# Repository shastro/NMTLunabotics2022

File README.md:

# NMTLunabotics2022
Primary Repository for All Software related to NMT Lunabotics 2022.

Please check the docs folder for relevant documentation and store user code in the user folder.

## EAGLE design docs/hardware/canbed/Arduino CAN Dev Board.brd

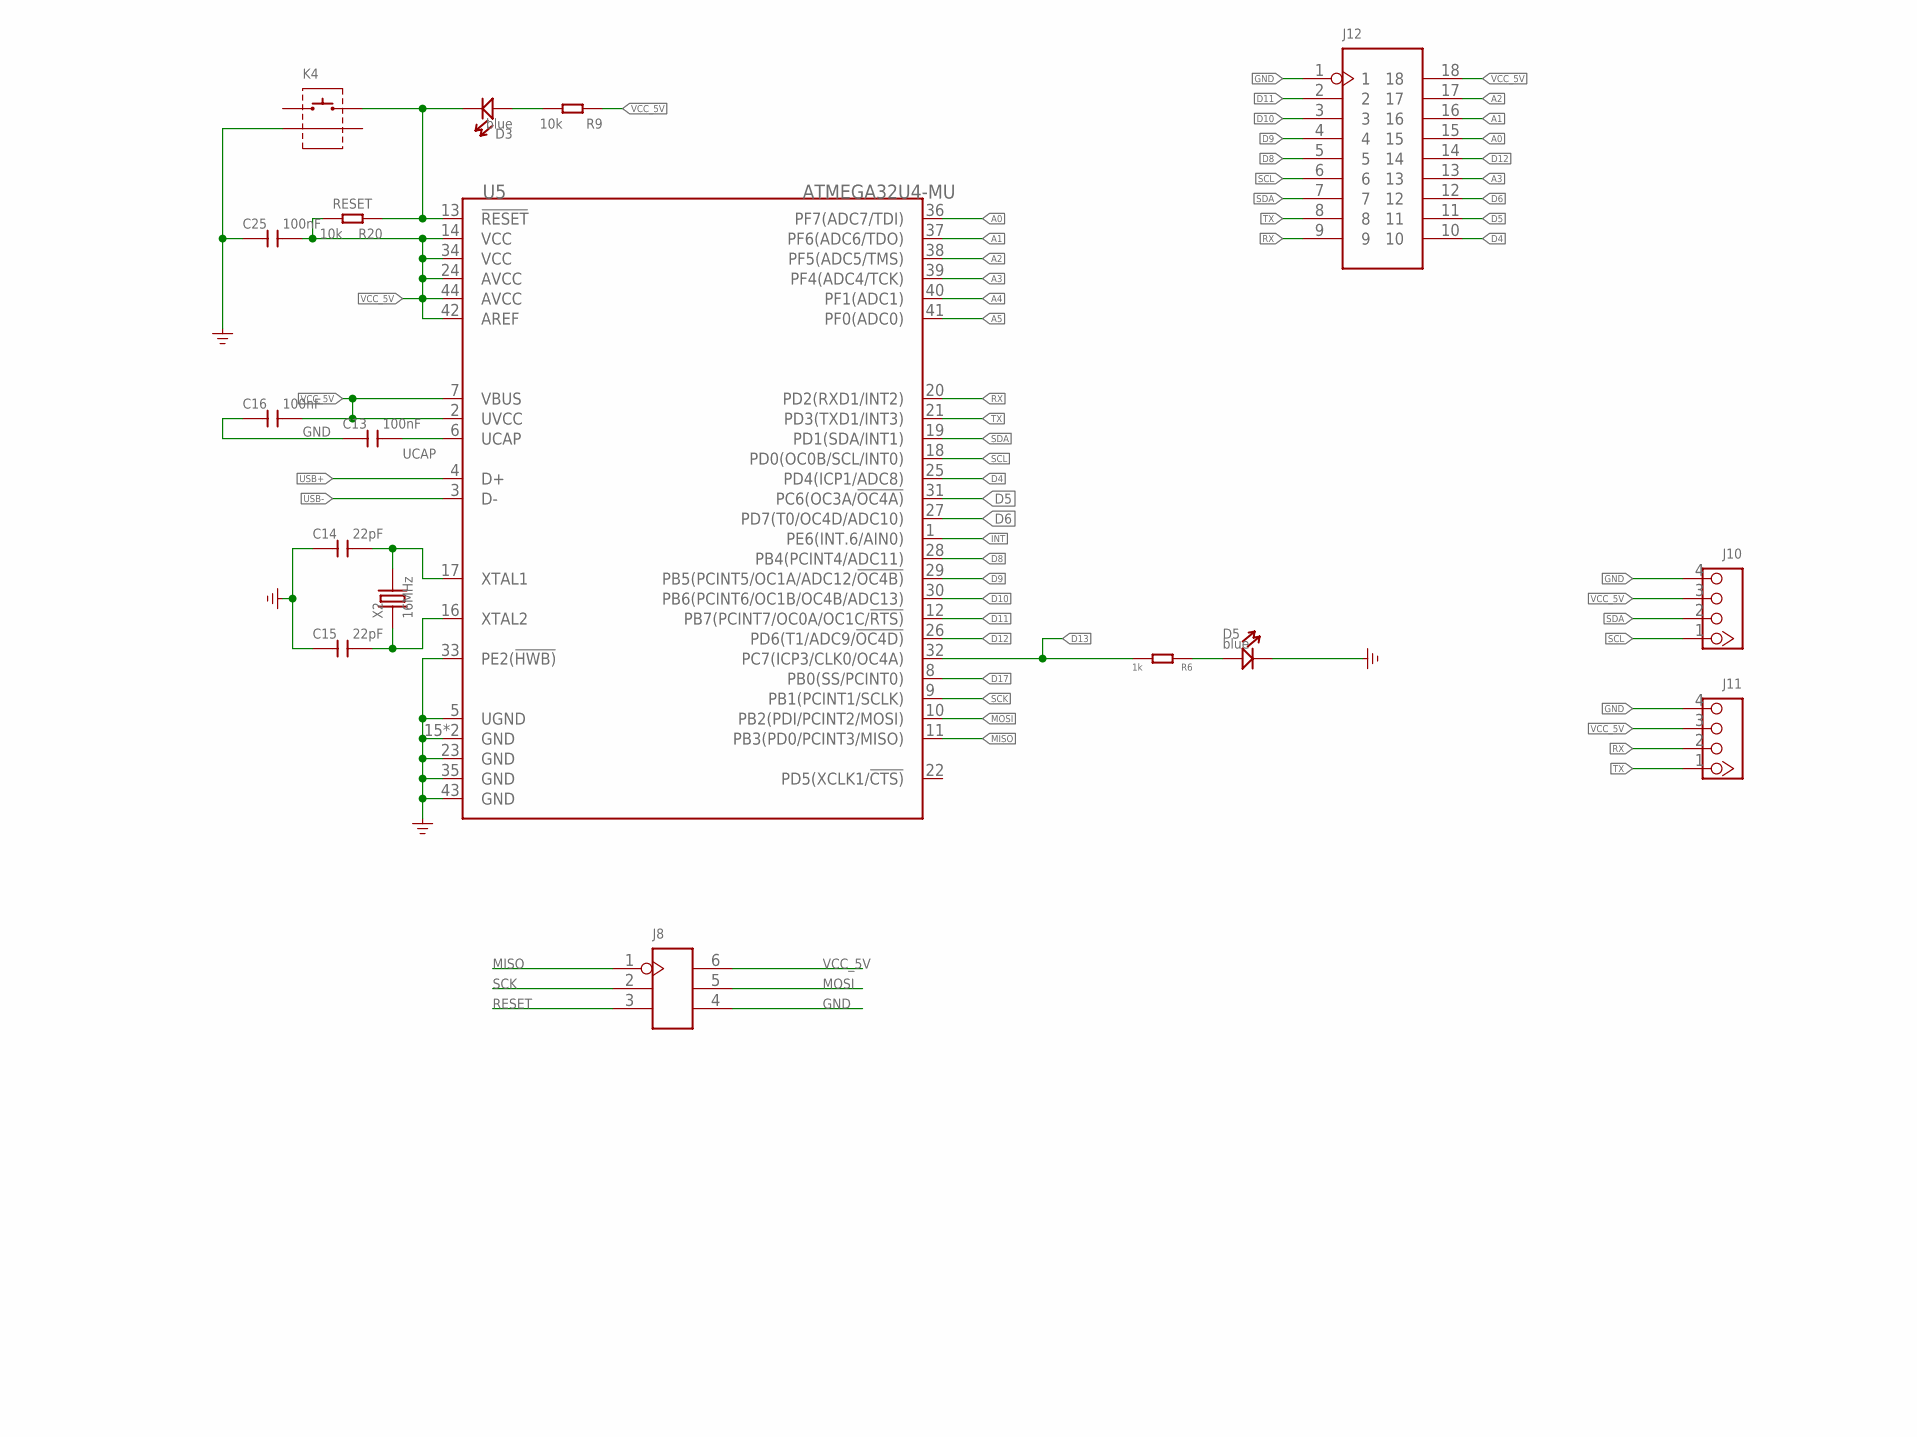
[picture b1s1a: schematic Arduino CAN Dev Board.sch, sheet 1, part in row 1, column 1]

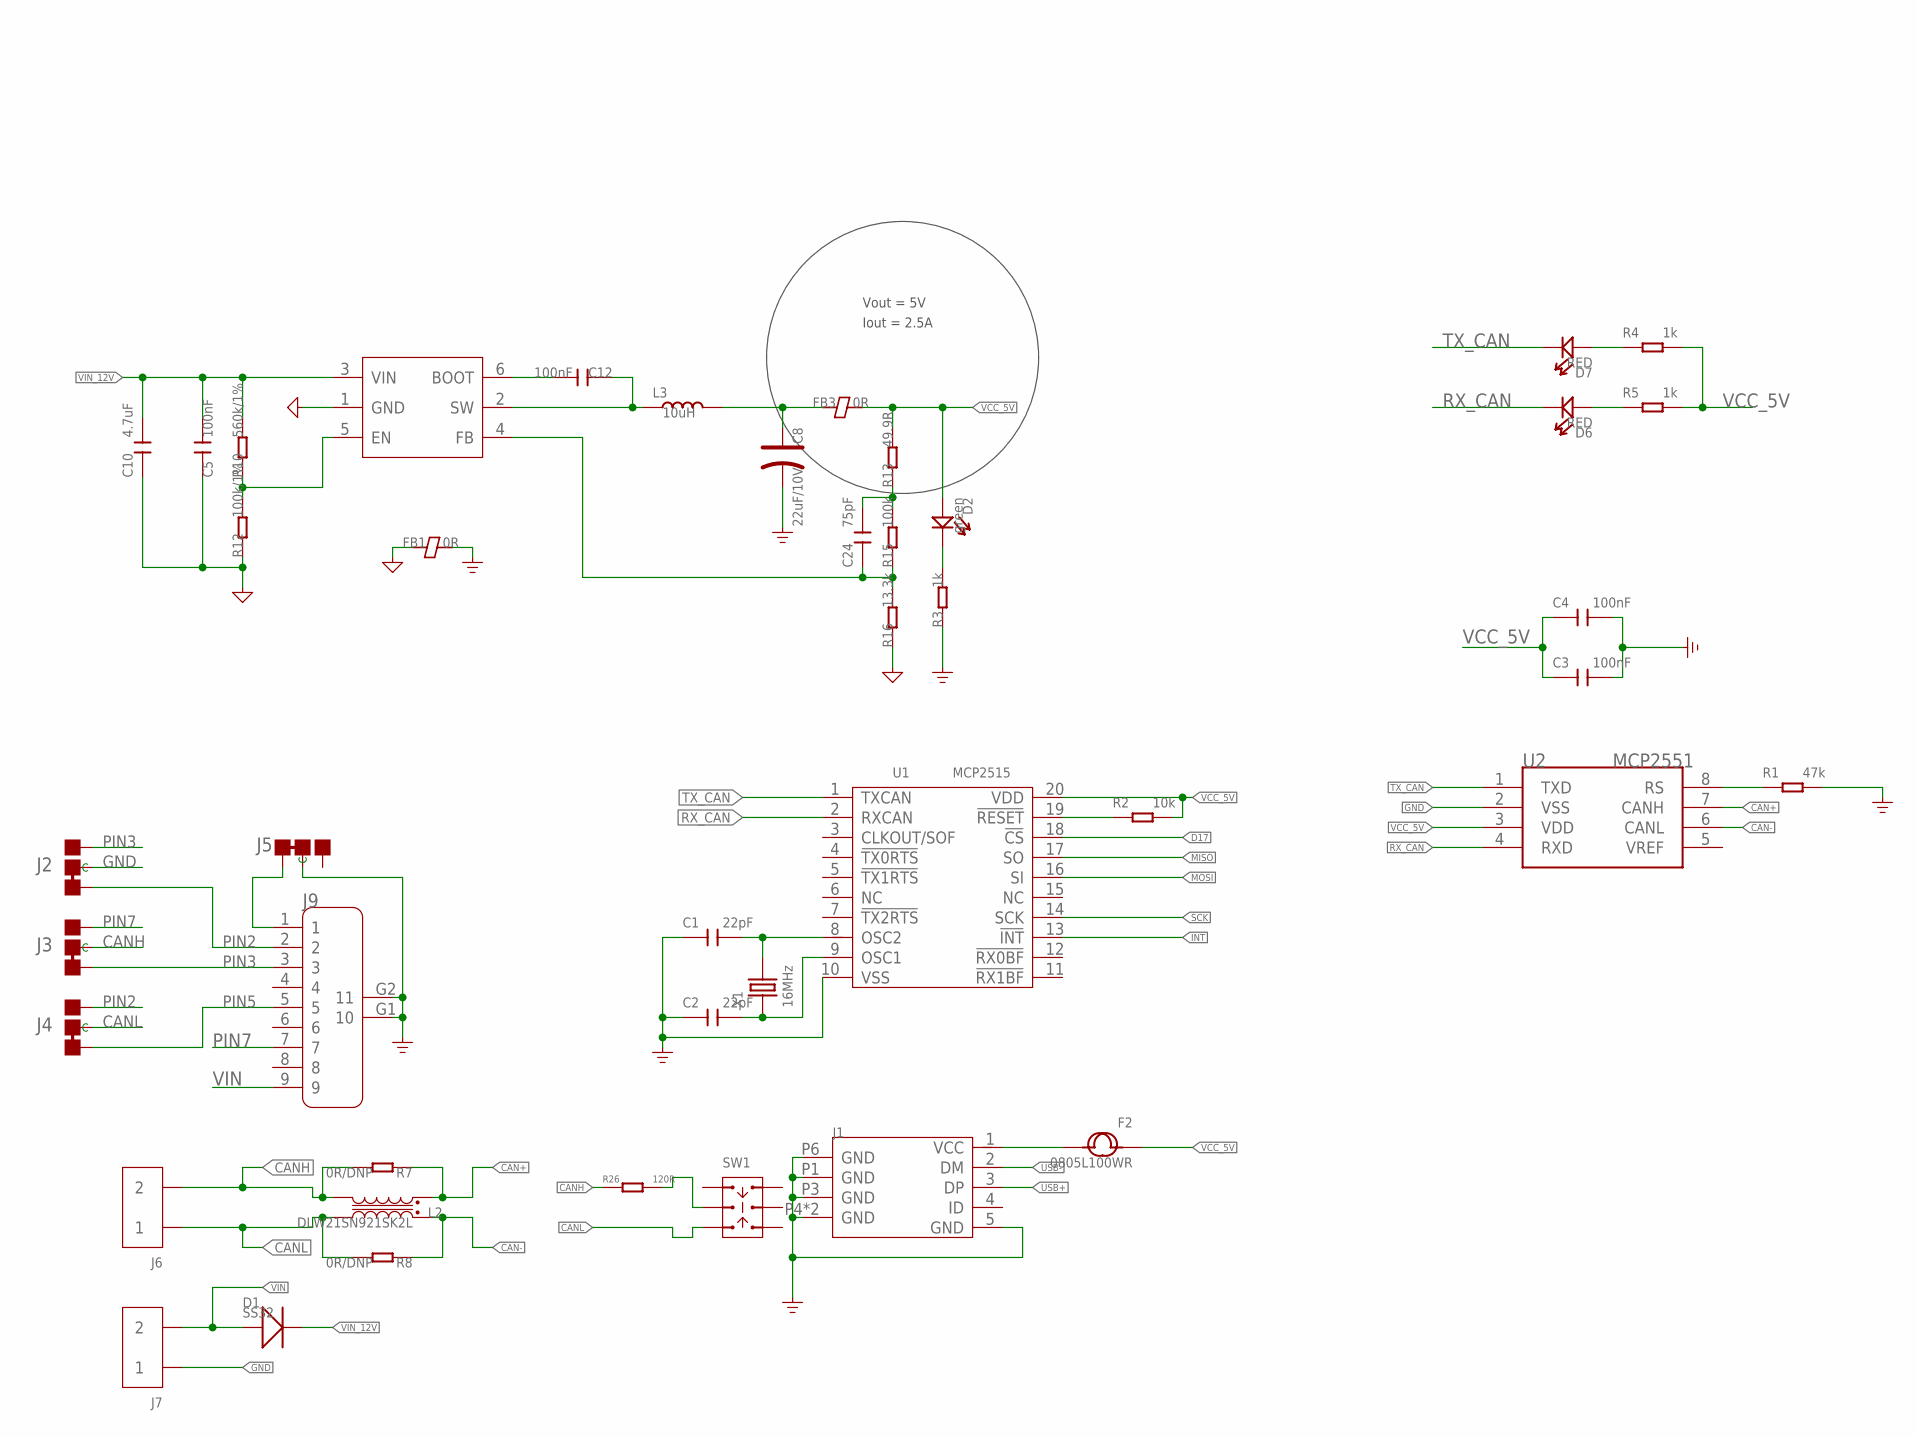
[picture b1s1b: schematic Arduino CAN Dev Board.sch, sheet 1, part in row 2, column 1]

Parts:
C1, C2, C14, C15: 22pF; C0603
C3, C4, C5, C12, C13, C16, C25: 100nF; C0603
C8: 22uF/10V; AVX-B
C10: 4.7uF; C1206
C24: 75pF; C0603
D1: SS32; DO-214AC
D2: green; LED-0603
D3, D5: blue; LED-0603
D6, D7: RED; LED-0603
F2: 0805L100WR; F0805
FB1, FB3: 0R; F0805
J1: MICRO-USB5+4P-320010050; MICRO-USB5+5P-SMD-0.65-7.2X5.06MM
J2, J3, J4, J5: JUMPER-3P-SHORT; 3P-SMD-SHORT
J6, J7: SCREW-TERMINAL-2P'5.08'; H2-5.0-10.5X8.0MM
J8: HEADER-2X3P-2.54; H2X3-2.54
J9: DB9'MEAL'; DB9-MEAL
J10, J11: 320110033; HW4-2.0
J12: HEADER-2X9P-2.54; H2X9-2.54
K4: BUTTON-2+2P; SW2+2P-7.7X2.75X3.95MM
L2: DLW21SN921SK2L; INT4-0.85-2X1.25X1.2MM
L3: 10uH; INT2-SMD-6.6X7.1X3MM
R1: 47k; R0603
R2, R9, R20: 10k; R0603
R3, R4, R5, R6: 1k; R0603
R7, R8: 0R/DNP; R0603
R10: 560k/1%; R0603
R12: 100k/1%; R0603
R13: 49.9R; R0603
R15: 100k; R0603
R16: 13.3k; R0603
R26: 120R; R0603
SW1: SWITCH-2CH-6P-311010004; SW6-2.54-9.0X3.5X3.2+2.0MM
U1: MCP2515; TSSOP20-0.65-6.5X4.4MM
U2: MCP2551; SOIC8-6.0
U5: ATMEGA32U4-MU; QFN44
U$11: PMIC-TPS54302; SOT-23-6
X1: 16MHz; X2-SMD-5.0X3.2X1.3MM
X2: 16MHz; 2P-SMD-5X3.2

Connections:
A0: J12.15, U5.36 (PF7(ADC7/TDI))
A1: J12.16, U5.37 (PF6(ADC6/TDO))
A2: J12.17, U5.38 (PF5(ADC5/TMS))
A3: J12.13, U5.39 (PF4(ADC4/TCK))
A4: U5.40 (PF1(ADC1))
A5: U5.41 (PF0(ADC0))
AGND: C5.1, C10.1, FB1.1, R12.1, R16.1, U$11.1 (GND)
CAN+: L2.4, R7.1, U2.7 (CANH)
CAN-: L2.1, R8.1, U2.6 (CANL)
CANH: J3.MM (C), J6.2, L2.3, R7.2, R26.1
CANL: J4.MM (C), J6.1, L2.2, R8.2, SW1.CH1B
D4: J12.10, U5.25 (PD4(ICP1/ADC8))
D5: J12.11, U5.31 (PC6(OC3A/!OC4A))
D6: J12.12, U5.27 (PD7(T0/OC4D/ADC10))
D8: J12.5, U5.28 (PB4(PCINT4/ADC11))
D9: J12.4, U5.29 (PB5(PCINT5/OC1A/ADC12/!OC4B))
D10: J12.3, U5.30 (PB6(PCINT6/OC1B/OC4B/ADC13))
D11: J12.2, U5.12 (PB7(PCINT7/OC0A/OC1C/!RTS))
D12: J12.14, U5.26 (PD6(T1/ADC9/!OC4D))
D13: R6.2, U5.32 (PC7(ICP3/CLK0/OC4A))
D17: U1.18 (!CS), U5.8 (PB0(SS/PCINT0))
EXT_PWR: F2.2, J1.1 (VCC)
GND: C1.1, C2.1, C3.2, C4.2, C8.-, C13.1, C14.1, C15.1, C16.1, C25.1, D5.-, FB1.2, J1.5 (GND), J1.P1 (GND), J1.P3 (GND), J1.P4 (GND), J1.P5 (GND), J1.P6 (GND), J2.MM (C), J5.MM (C), J7.1, J8.4, J9.G1 (10), J9.G2 (11), J10.4, J11.4, J12.1, K4.S1, R1.2, R3.1, U1.10 (VSS), U2.2 (VSS), U5.5 (UGND), U5.15 (GND), U5.23 (GND), U5.33 (PE2(!HWB)), U5.35 (GND), U5.43 (GND), U5.TAB (GND)
INT: U1.13 (!INT), U5.1 (PE6(INT.6/AIN0))
MISO: J8.1, U1.17 (SO), U5.11 (PB3(PD0/PCINT3/MISO))
MOSI: J8.5, U1.16 (SI), U5.10 (PB2(PDI/PCINT2/MOSI))
unnamed: D2.-, R3.2
unnamed: D7.+, R4.1
unnamed: D3.+, R9.2
unnamed: R10.1, R12.2, U$11.5 (EN)
unnamed: R26.2, SW1.COM1
unnamed: C14.2, U5.17 (XTAL1), X2.2
unnamed: D5.+, R6.1
unnamed: C12.1, L3.1, U$11.2 (SW)
unnamed: C15.2, U5.16 (XTAL2), X2.1
unnamed: J5.11 (L), J9.1
unnamed: C12.2, U$11.6 (BOOT)
unnamed: D6.+, R5.1
unnamed: C1.2, U1.8 (OSC2), X1.2
unnamed: C2.2, U1.9 (OSC1), X1.1
unnamed: C8.+, FB3.1, L3.2
unnamed: R1.1, U2.8 (RS)
unnamed: C24.2, R13.1, R15.2
unnamed: C24.1, R15.1, R16.2, U$11.4 (FB)
PIN2: J2.11 (L), J4.00 (R), J9.2
PIN3: J2.00 (R), J3.11 (L), J9.3
PIN5: J4.11 (L), J9.5
PIN7: J3.00 (R), J9.7
RESET: D3.-, J8.3, K4.2, R20.1, U5.13 (!RESET)
RST_N: R2.1, U1.19 (!RESET)
RX: J11.2, J12.9, U5.20 (PD2(RXD1/INT2))
RX_CAN: D6.-, U1.2 (RXCAN), U2.4 (RXD)
SCK: J8.2, U1.14 (SCK), U5.9 (PB1(PCINT1/SCLK))
SCL: J10.1, J12.6, U5.18 (PD0(OC0B/SCL/INT0))
SDA: J10.2, J12.7, U5.19 (PD1(SDA/INT1))
TX: J11.1, J12.8, U5.21 (PD3(TXD1/INT3))
TX_CAN: D7.-, U1.1 (TXCAN), U2.1 (TXD)
UCAP: C13.2, U5.6 (UCAP)
USB+: J1.3 (DP), U5.4 (D+)
USB-: J1.2 (DM), U5.3 (D-)
VCC_5V: C3.1, C4.1, C16.2, C25.2, D2.+, F2.1, FB3.2, J8.6, J10.3, J11.3, J12.18, R2.2, R4.2, R5.2, R9.1, R13.2, R20.2, U1.20 (VDD), U2.3 (VDD), U5.2 (UVCC), U5.7 (VBUS), U5.14 (VCC), U5.24 (AVCC), U5.34 (VCC), U5.42 (AREF), U5.44 (AVCC)
VIN: D1.1 (+), J7.2, J9.9
VIN_12V: C5.2, C10.2, D1.2 (-), R10.2, U$11.3 (VIN)

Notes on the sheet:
Vout = 5V
Iout = 2.5A

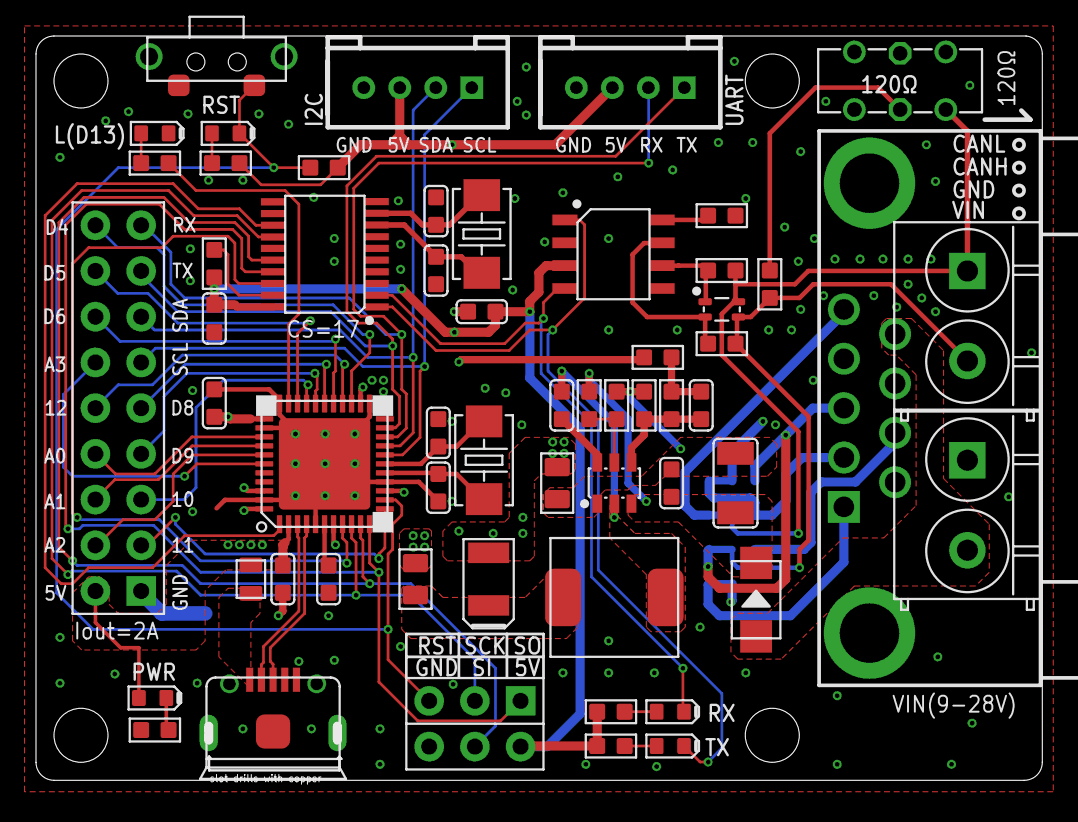
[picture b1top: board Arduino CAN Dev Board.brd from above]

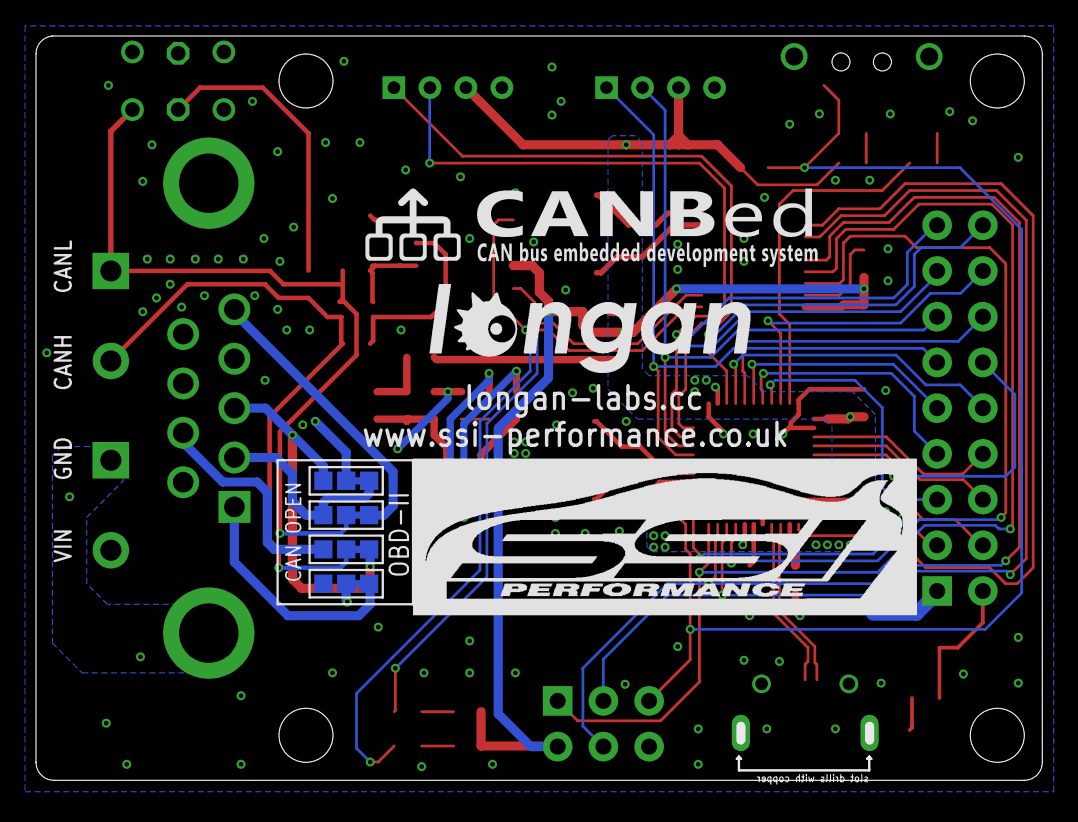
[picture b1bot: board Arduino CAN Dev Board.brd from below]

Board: 2 copper layers, 55.4 x 41.2 mm, 62 parts (5 on the bottom side), 61 nets.

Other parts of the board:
U$12: LONGAN-SILK-SMALL

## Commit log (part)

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2021-10-28 Add c generation tests as well as a script for generating linear maps for use in the kcd files. Add first successful custom kcd file x.kcd
2021-10-29 Add preliminary can2canarray code (Currently just recieves can msgs via socketcan. Add testing kcd file x.kcd. Add CAN interface setupscript
2021-10-31 Speed controls in robot_kbd
2021-10-31 Make robot resemble Lunabotics slightly better
    I'm using four wheels on each side to try and vaguely approximate
    how treads will operate.
2021-11-09 Fix controller node name
2021-11-09 Restructure CAN demos
2021-11-10 Use vector of wheels
2021-11-13 Probably fix compilation issues on Ubuntu
    There's an issue with the generic syntax I'm using on the Ubuntu C++
    compiler. This should /probably/ fix it, but I'm not 100% sure.
2021-11-17 Put some sensors on the robot
2021-11-18 Add .weproj file
2021-11-23 :memo: Shameless change to test gitmoji don't @me
2021-11-25 Update Ubuntu20_Demo_Instructions.md
    Add ROS install instructions
2021-11-25 Update Ubuntu20_Demo_Instructions.md
    Add Webots, ROS, and Demo sections
2021-11-25 Update Ubuntu20_Demo_Instructions.md
    Update Readme
2022-01-04 Move to catkin workspace, create user directory with tutorial files
2022-01-21 Update Ubuntu20_Demo_Instructions.md
    Updated the directory pointing to robot_kbd
2022-01-28 Add rplidar_ros
2022-01-28 Fix robot_kbd quitting behavior
    No idea why it was like that originally, but it was bugging me.
2022-01-30 Update Readme.md
    Testing webhook
2022-01-30 Start base controller dev
2022-01-30 Write base controller
2022-01-30 Fix copyright
2022-01-31 Add `cmd-vel-path` argument to base controller
2022-01-31 Add nav_dummy program for testing base controller
2022-02-02 Update lidardemo to Webots 2022a
    Update wheel rotations to FLU/ENU axis system; this will be
    incompatible with 2021b (the previous version), so everyone will have
    to update.
2022-02-04 Add launch file. Add aruco tests.
2022-02-04 abethel: add formatting script
2022-02-04 Factor out transforms into their own launch file
2022-02-04 Add webcam support for arucoTest
2022-02-06 :bulb: Add launch comment
2022-02-08 Add aruco tests, Add sim tests
2022-02-09 Nav stack config work (still not quite done)
2022-02-10 Fix tf issue. Add maps.
2022-02-10 Update use tf2 instead of tf
2022-02-10 :beers: Move files, Correct parameters for robot nav stack configs.
2022-02-10 Fix transforms
2022-02-10 Move launch, maps, configs,rviz, etc to ros package
2022-02-10 Remove extra files
2022-02-11 Fix sim launch file
2022-02-11 Update params, moving towards navstack in webots
2022-02-12 Formatting
2022-02-18 Move TLDR to docs
2022-02-18 Update tldr
2022-02-25 Fix sim models
2022-02-25 Update world
2022-02-28 Remove inner set of 4 wheels on simulation robot
    This commit removes wheels 5, 6, 7, and 8 on all the simulation
    robots, and removes all code that controls those wheels from
    base_controller and robot_kbd. This should provide a starting point
    for fixing the issues with slipping when the robot is navigating.
2022-03-14 Add tracks to TEST_FLAT Webots file
    Have yet to get them actually spinning correctly.
2022-03-18 Updates to robots. Have made a new robot in tracked_animated.wbt but it still does not move
2022-03-18 Replaced old robot with new robot
2022-03-18 Added robots folder to make it easier to modify and import david into different worlds
2022-03-21 Automatically load the RVIZ configuration
2022-03-21 Straighten camera orientation in TEST_FLAT
    It was really bugging me :P
2022-03-22 Set up `sim_basic.sh` with the laser
    Mapping seems to work again :)
2022-03-22 Update rviz config for sim
2022-03-22 Get `move_base` working on current robot
    For some reason it spins around forever rather than actually
    navigating, but it is apparently running.
2022-03-23 Movebase working. Update footprint. Update rviz
2022-03-23 Update rviz update global costmap
2022-03-23 Set motor radius to theoretically correct value
    Hmm
2022-03-31 Update costmap params
2022-03-31 Add new hardware docs
2022-03-31 Add aruco experiments
2022-04-05 Add system parts blend files
2022-04-05 Removed extra files
2022-04-07 Fix rplidar_ros not existing
2022-04-09 Add bluetooth controller experiments, motor experiments, and action server experiments
2022-04-09 Replace `backup` with `rpi-clone`
2022-04-09 Clean up base_controller code
2022-04-10 Implement basic motor control over bluetooth. Needs refactoring and code organization
2022-04-15 Rename folder
2022-04-15 Fix folder name
2022-04-15 Fixed? xr_usb_serial_common driver error
2022-04-15 Fix typo in driver
2022-04-15 Start Teknic integration in base_controller
2022-04-15 Wheee broken dependencies
2022-04-15 Remove more Webots dependencies
2022-04-16 More work on Teknic base_controller integration
2022-04-16 Refactor motor_bluetooth stuff
2022-04-17 Add setNodePos function to motor_bluetooth
2022-04-17 Write Raspberry Pi GPIO library
2022-04-18 GPIO input & output pin abstraction
2022-04-19 Don't tear the robot apart, Alex
2022-04-19 Fix rpm
2022-04-20 Update motor values
2022-04-20 Fix incorrect comments
2022-04-20 Override motor velocity to -5
2022-04-20 Debugging shenanigans
2022-04-26 Fix `joystick.cc` move constructor unsoundness
    If I ever get around to it I'll file a bug report with the original
    library that the move constructor is unsound.
2022-04-27 Remove moveNodesFixed -> setAllNodeVel
2022-04-27 Remove comments
2022-04-27 Ensure ports disable motors before disconnecting
    Previous code likely caused a soundness bug.
2022-04-27 Motor lib documentation
2022-04-29 Reorganize motor_bluetooth
2022-04-30 Add camera test
2022-04-30 Remove object files accidentally included
2022-04-30 Use move semantics on nodes & ports
2022-05-10 Add abethel test_workspace
2022-05-11 Add fibonacci client
2022-05-11 Write compile commands
2022-05-11 david_action Navigation action stuff
2022-05-11 Update webots worlds
2022-05-11 Add david_waypoints skeleton
2022-05-11 Fix incorrect david_waypoints CMakeLists
2022-05-11 Update parameters and movebase
2022-05-11 Write skeleton pitch action
2022-05-12 Update motor_bluetooth for temporary setup
2022-05-12 Set up for test without dump motors
2022-05-12 Teknic ROS integration
2022-05-12 Update navigation
2022-05-12 Fix error handling in motor_bluetooth
2022-05-12 Fix EnableReq
2022-05-12 Increase locomotion velocity
2022-05-12 Fix same bug in base_controller
2022-05-12 Add motor property reads
2022-05-12 Add rms level
2022-05-13 More error handling 😤
2022-05-13 Code formatting
2022-05-13 Use symlinks for motor_lib
2022-05-13 Add cvcam.py
2022-05-13 Navigation server implementation skeleton
2022-05-13 Remove old aruco test
2022-05-13 Add urdfs
2022-05-13 Use image_transport
2022-05-13 Add dump tranforms
2022-05-14 Create pitch_controller package
2022-05-14 Write pitch test under user/abethel
2022-05-14 Emergency commit
2022-05-14 Better pitch test UI
2022-05-14 Fix raspberry pi GPIO race condition >:(
2022-05-14 Add pitch assembly
2022-05-14 Improve joint naming convention
2022-05-14 Update pitch controller
2022-05-14 Update urdfs
2022-05-14 david_action pitch GPIO support
2022-05-14 Typo
2022-05-14 Wait 50 seconds for pitch changes
2022-05-14 Add comments
2022-05-14 Add test_urdf.launch
2022-05-15 Added script to point ROS_MASTER_URI at demo pi
2022-05-15 Action tests program
2022-05-15 Fix waiting for action server
2022-05-15 Fix angle in pitch server
2022-05-15 Finish params
2022-05-15 Update launch file and urdf
2022-05-15 Fix joint state launch file
2022-05-15 Add progress
2022-05-15 Finalize progress on pitch action server
2022-05-15 Teknic motor manager to prevent RMS overload
2022-05-15 Fix float cast
2022-05-15 Fix clock bug
2022-05-15 Add print statement
2022-05-15 Fix clock thingy
2022-05-15 Add debug print
2022-05-15 Update time_wait signature
2022-05-15 Move base_controller to david_motor directory
2022-05-15 Replace base_controller in temp_sim.launch
2022-05-15 Fix sign error
2022-05-15 Add new david_motor message defs
2022-05-15 Fix input handling
2022-05-15 Fix compilation error
2022-05-15 Add david_hello network test package
2022-05-15 Change image encoding
2022-05-16 Add udp options to prevent overrun errors
2022-05-16 Adding hardware timer interrupts for status LED. LED now blinks when device in standby; solid when enable pin held high.
2022-05-16 Added shell script for updating Arduino code. Script copiles latest version of .ino code and programs the Arduino.
2022-05-16 Add camera utility program skeleton. Update Waypoints.
2022-05-16 Fix merge aaaaaaaa
2022-05-16 Added verbose flag to Arduino programming script.
2022-05-16 Fix CMakeLists
2022-05-16 Added interrupt-driven enable pin polling. The state of the enable pin is now polled at 2kHz using timer interrupt. Enable pin state is also debounced.
2022-05-16 Fix udp string
2022-05-16 Fixed erroneous mode input evaluation.
2022-05-16 Separate out cmd_auger and cmd_dump
2022-05-16 Add camera calibration and update testing utils
2022-05-16 Remove fifo_size as it seems to be another source of delay
2022-05-16 Further camera property adjustments
2022-05-16 Get david_gamepad working
2022-05-17 Adjust udp options
2022-05-17 💩 Implement david_motor APIs
2022-05-17 Use <> instead of "" in david_motor
    may or may not resolve build issues
2022-05-17 Fix david_gamepad depth commands
2022-05-17 Update projection axis
2022-05-17 Functionalized actuator control scheme.
2022-05-17 In Arduino code, made HalfExtend() state-aware. Also accounted for transition from full-extend to half-extend states.
2022-05-17 Error correction in motors
2022-05-17 Update arduino code for fancy shmancy H-bridges
2022-05-17 Revert reversion because cringe
    This reverts commit ace081bc785aba129d058d3d1476a0e535715b0c.
2022-05-17 Heavily simplify pitch motor controller arduino code
    It wasn't working, so I deleted half the program rather than debugging
    it because we don't have enough time to get full functionality.
2022-05-17 Update david_action pitch to new conventions
2022-05-17 Fix camera argument parsing. Add launch files
2022-05-17 Set pitch motor time to 20 seconds
2022-05-18 Increase gamepad auger speed
2022-05-18 Write david_pitch
2022-05-18 Make camera nodes anonymous
2022-05-18 Remove unnecessary includes
2022-05-18 Temporarily disable start_vision_system.launch's extra functionality
2022-05-18 Fix arguments in waypoints
2022-05-18 Add configs
2022-05-18 Add debug prints
2022-05-22 New scripts and renaming files
2022-05-22 Fix emergency stop false positives
2022-05-22 Swap incorrect direction of depth and dump
2022-05-22 Swap x direction on gamepad motion
2022-05-22 Modified script to work on AI cpu instead of local machine
2022-05-22 Add script for starting control system
2022-05-22 Add ai system start script
2022-05-22 Add telemetry system
2022-05-22 Update pitch error
2022-05-22 Minor script updates
2022-05-23 Update ai script
2022-05-23 Add script for changing SSID
2022-05-23 Modified rpilidar launch
2022-05-23 Change tty
2022-05-23 Add competition mapping launch file
2022-05-23 Add static transform
2022-05-23 Fix dumb bug in `setssid`
2022-05-23 Fix start_ai_system incorrect blank line
2022-05-23 Make `david_gamepad` start up ROS &c. if necessary
2022-05-23 Update constants
2022-05-23 Update visualization script
2022-05-23 Switch locomotion control to left thumb
2022-05-23 Update auger conversions
2022-05-23 Fix gearbox
2022-05-24 Update telemetry
2022-05-24 Decrease locomotion speed
2022-05-24 Motor-lib parallelism testing
2022-05-24 More error handling
2022-05-24 Format everything
2022-05-24 Make david_motor build again
    Use pointers instead of references, because I'm on a ridiculous
    deadline and can't figure out the problem.
2022-05-24 Reduce resolution
2022-05-24 Update res
2022-06-09 Update RPM
2022-08-25 Update motor manager resolution from 2 to 5 Hz
2022-09-20 Start playing with Docker scripts
    Made a Dockerfile that compiles the Lunabotics code into an image; it
    compiles so long as you remove `david_waypoints` (which should be
    fixed soon, hopefully).
    tmp
2022-09-20 Fix bug with early exit when failing to prune images
2022-10-07 Remove david_waypoints from docker branch
    The whole system doesn't build when david_waypoints is present at the
    moment; I'm moving it to its own branch until it compiles.
2022-10-08 Update compile_flags.txt things
2022-10-08 Oops, I broke the build process
2022-10-10 Fix /etc/hosts problems in Docker
2022-10-11 Add setssid stuff to gamepad script
